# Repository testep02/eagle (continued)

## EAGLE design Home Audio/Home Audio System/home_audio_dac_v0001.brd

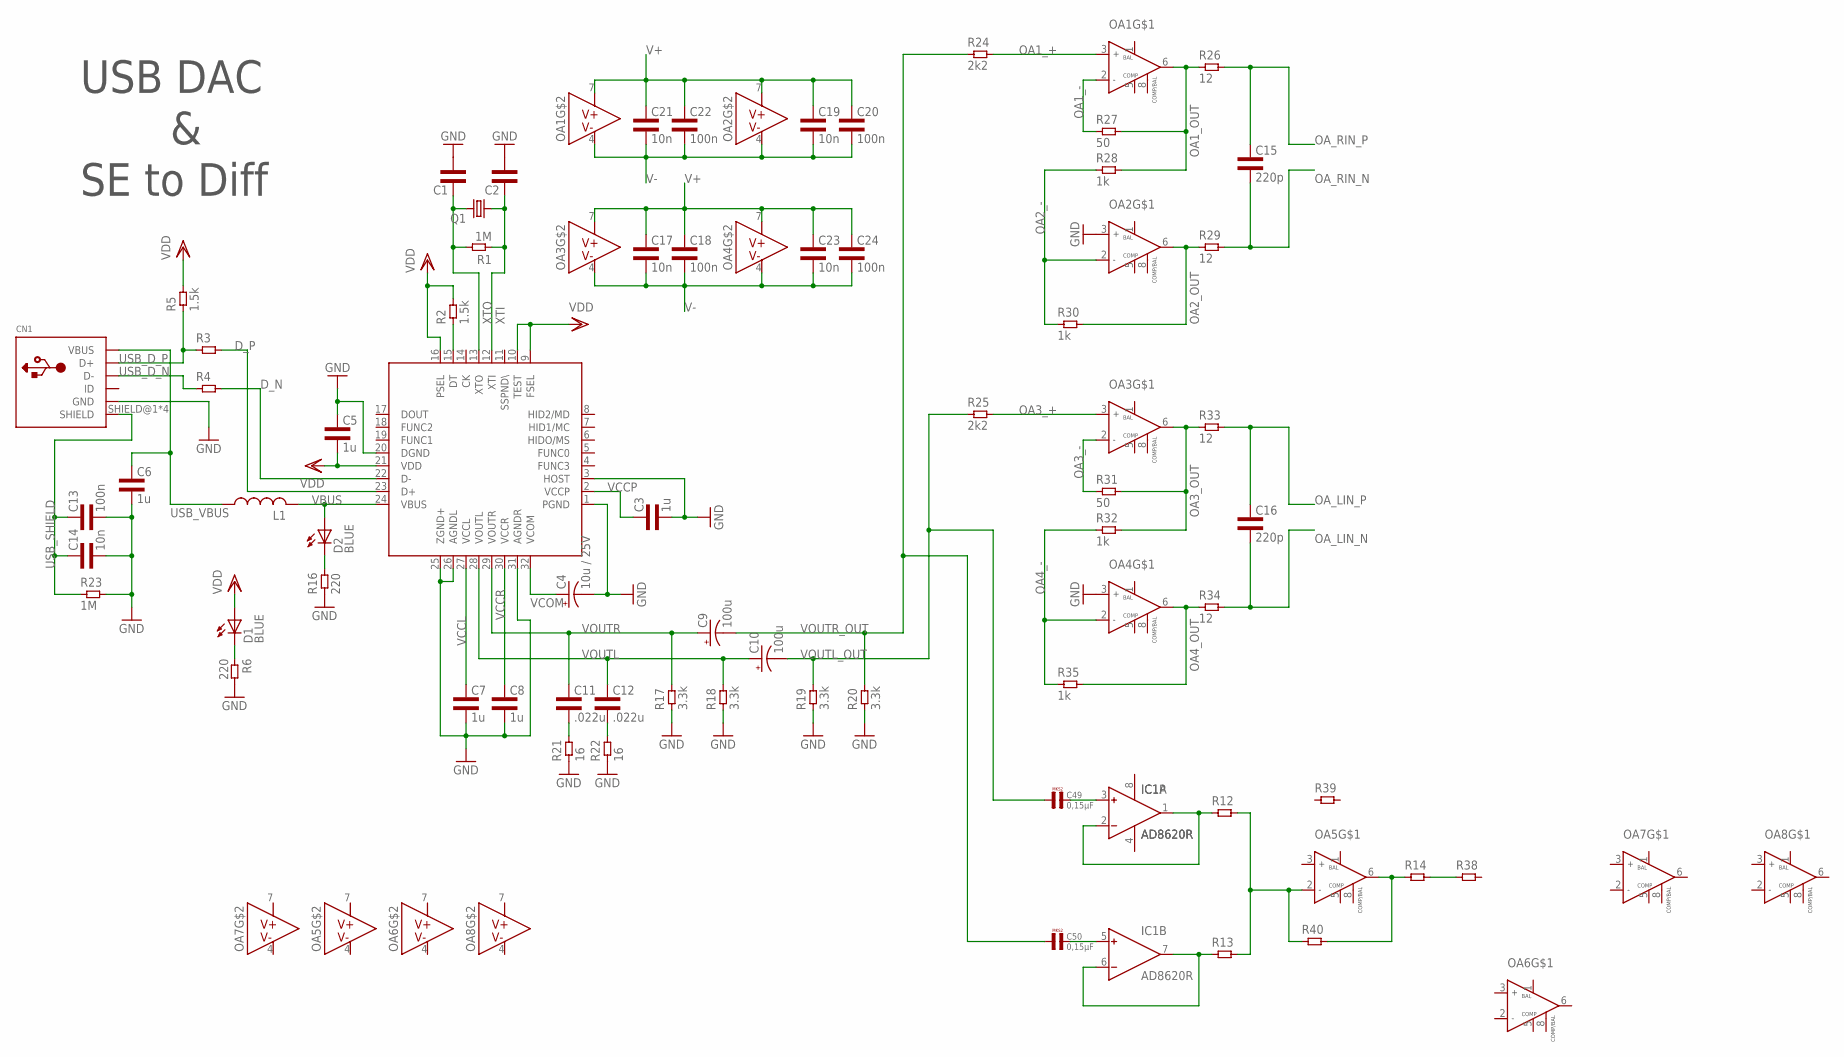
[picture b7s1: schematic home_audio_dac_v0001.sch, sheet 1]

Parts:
C1, C2: CAP0603L3; 0603L3
C3, C5, C6, C7, C8: 1u; 0603L3
C4: 10u / 25V; E1,8-4
C9, C10: 100u; E2-5
C11, C12: .022u; 0603L3
C13, C18, C20, C22, C24: 100n; 0603L3
C14, C17, C19, C21, C23: 10n; 0603L3
C15, C16: 220p; 0603L3
C49, C50: 0,15µF; R5B2K5
CN1: USBMINIB; USB-MINIB
D1, D2: BLUE; LED-0603
IC1: AD8620R; SO8
L1: RCL_L-USL3225M; RCL_L3225M
OA1, OA2, OA3, OA4: NE5534ADSOIC8; SOIC-8
OA5, OA6, OA7, OA8: NE5534SOIC8; SOIC-8
Q1: PCM2707_V1_SPARKFUN_CRYSTALHC49US; PCM2707_V1_SPARKFUN_HC49US
R1, R23: 1M; 0603L3
R2, R5: 1.5k; 0603L3
R3, R4, R12, R13, R14, R38, R39, R40: RES0603L3; 0603L3
R6, R16: 220; 0603L3
R17, R18, R19, R20: 3.3k; 0603L3
R21, R22: 16; 0603L3
R24, R25: 2k2; 0603L3
R26, R29, R33, R34: 12; 0603L3
R27, R31: 50; 0603L3
R28, R30, R32, R35: 1k; 0603L3
U$1: PCM2707_V1_PCM2704C_PCM2707

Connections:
DT: R2.P$1 (1), U$1.15 (DT)
D_N: R4.P$2 (2), U$1.22 (D-)
D_P: R3.P$2 (2), U$1.23 (D+)
GND: C1.P$2 (2), C2.P$2 (2), C3.P$2 (2), C4.-, C5.P$1 (1), C6.P$2 (2), C7.P$2 (2), C8.P$2 (2), C13.P$2 (2), C14.P$2 (2), CN1.GND, OA2.3 (IN+), OA4.3 (IN+), R6.P$2 (2), R16.P$1 (1), R17.P$1 (1), R18.P$1 (1), R19.P$1 (1), R20.P$1 (1), R21.P$1 (1), R22.P$1 (1), R23.P$2 (2), U$1.1 (PGND), U$1.3 (HOST), U$1.20 (DGND), U$1.25 (ZGND+), U$1.26 (AGNDL), U$1.31 (AGNDR); also elsewhere on the board
unnamed: C49.2, IC1.3 (IN+)
unnamed: C50.2, IC1.5 (IN+)
unnamed: IC1.1 (OUT), IC1.2 (IN-), R12.P$1 (1)
unnamed: IC1.6 (IN-), IC1.7 (OUT), R13.P$1 (1)
unnamed: OA5.2 (IN-), R12.P$2 (2), R13.P$2 (2), R40.P$1 (1)
unnamed: OA5.6 (OUT), R14.P$1 (1), R40.P$2 (2)
unnamed: R14.P$2 (2), R38.P$1 (1)
unnamed: D2.C, R16.P$2 (2)
OA1_+: OA1.3 (IN+), R24.P$2 (2)
OA1_-: OA1.2 (IN-), R27.P$1 (1)
OA1_OUT: OA1.6 (OUT), R26.P$1 (1), R27.P$2 (2), R28.P$2 (2)
OA2_-: OA2.2 (IN-), R28.P$1 (1), R30.P$1 (1)
OA2_OUT: OA2.6 (OUT), R29.P$1 (1), R30.P$2 (2)
OA3_+: OA3.3 (IN+), R25.P$2 (2)
OA3_-: OA3.2 (IN-), R31.P$1 (1)
OA3_OUT: OA3.6 (OUT), R31.P$2 (2), R32.P$2 (2), R33.P$1 (1)
OA4_-: OA4.2 (IN-), R32.P$1 (1), R35.P$1 (1)
OA4_OUT: OA4.6 (OUT), R34.P$1 (1), R35.P$2 (2)
OA_LIN_N: C16.P$2 (2), R34.P$2 (2); also elsewhere on the board
OA_LIN_P: C16.P$1 (1), R33.P$2 (2); also elsewhere on the board
OA_RIN_N: C15.P$2 (2), R29.P$2 (2); also elsewhere on the board
OA_RIN_P: C15.P$1 (1), R26.P$2 (2); also elsewhere on the board
USB_D_N: CN1.D-, R4.P$1 (1)
USB_D_P: CN1.D+, R3.P$1 (1), R5.P$1 (1)
USB_SHIELD: C13.P$1 (1), C14.P$1 (1), CN1.SHIELD@1 (SHIELD), CN1.SHIELD@2 (SHIELD), CN1.SHIELD@3 (SHIELD), CN1.SHIELD@4 (SHIELD), R23.P$1 (1)
USB_VBUS: C6.P$1 (1), CN1.VBUS, L1.1
V+: C17.P$1 (1), C18.P$1 (1), C19.P$1 (1), C20.P$1 (1), C21.P$1 (1), C22.P$1 (1), C23.P$1 (1), C24.P$1 (1), IC1.8 (V+), OA1.7 (V+), OA2.7 (V+), OA3.7 (V+), OA4.7 (V+), OA5.7 (V+), OA6.7 (V+), OA7.7 (V+), OA8.7 (V+)
V-: C17.P$2 (2), C18.P$2 (2), C19.P$2 (2), C20.P$2 (2), C21.P$2 (2), C22.P$2 (2), C23.P$2 (2), C24.P$2 (2), IC1.4 (V-), OA1.4 (V-), OA2.4 (V-), OA3.4 (V-), OA4.4 (V-), OA5.4 (V-), OA6.4 (V-), OA7.4 (V-), OA8.4 (V-)
VBUS: D2.A, L1.2, U$1.24 (VBUS)
VCCL: C7.P$1 (1), U$1.27 (VCCL)
VCCP: C3.P$1 (1), U$1.2 (VCCP)
VCCR: C8.P$1 (1), U$1.30 (VCCR)
VCOM: C4.+, U$1.32 (VCOM)
VDD: C5.P$2 (2), D1.A, R2.P$2 (2), R5.P$2 (2), U$1.9 (FSEL), U$1.10 (TEST), U$1.16 (PSEL), U$1.21 (VDD)
VDD_LED: D1.C, R6.P$1 (1)
VOUTL: C10.+, C12.P$1 (1), R18.P$2 (2), U$1.28 (VOUTL)
VOUTL_CAP: C12.P$2 (2), R22.P$2 (2)
VOUTL_OUT: C10.-, C49.1, R19.P$2 (2), R25.P$1 (1)
VOUTR: C9.+, C11.P$1 (1), R17.P$2 (2), U$1.29 (VOUTR)
VOUTR_CAP: C11.P$2 (2), R21.P$2 (2)
VOUTR_OUT: C9.-, C50.1, R20.P$2 (2), R24.P$1 (1)
XTI: C2.P$1 (1), Q1.1, R1.P$1 (1), U$1.12 (XTI)
XTO: C1.P$1 (1), Q1.2, R1.P$2 (2), U$1.13 (XTO)

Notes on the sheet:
USB DAC
SE to Diff

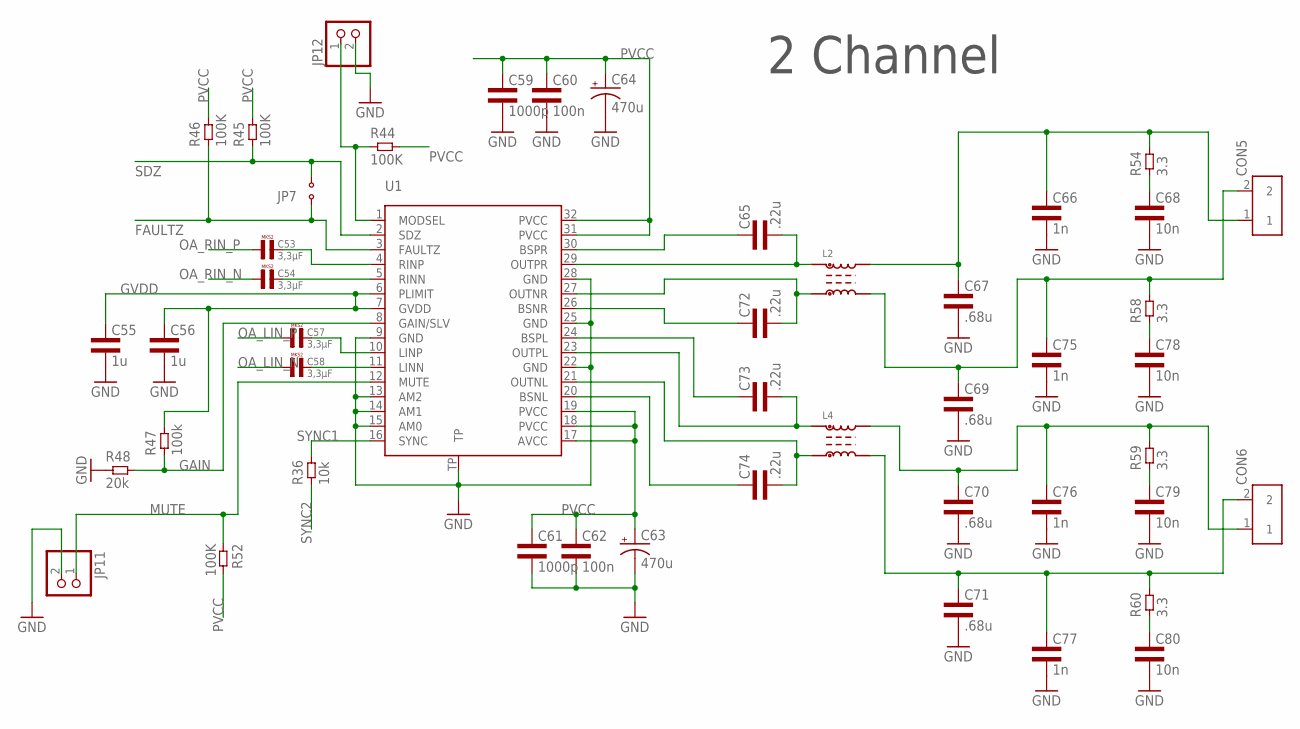
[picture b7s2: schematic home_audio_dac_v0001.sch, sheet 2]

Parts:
C53, C54, C57, C58: 3,3µF; R5B5K5
C55, C56: 1u; 0603L3
C59, C61: 1000p; 0805L3
C60, C62: 100n; 0805L3
C63, C64: 470u; PANASONIC_F
C65, C72, C73, C74: .22u; 0805L3
C66, C75, C76, C77: 1n; 0603L3
C67, C69, C70, C71: .68u; 1206L3
C68, C78, C79, C80: 10n; 0805L3
CON5, CON6: TERM_BLOCK_2
JP7: JUMPER2
JP11, JP12: PINHD-1X2; 1X02
L2, L4: 1155EA
R36: 10k; 0603L3
R44, R45, R46, R52: 100K; 0603L3
R47: 100k; 0603L3
R48: 20k; 0603L3
R54, R58, R59, R60: 3.3; 0805L3
U1: TPA3116; R-PDSO-32

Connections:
FAULTZ: JP7.1, R46.P$1 (1), U1.3 (FAULTZ); also elsewhere on the board
GAIN: R47.P$1 (1), R48.P$2 (2), U1.8 (GAIN/SLV); also elsewhere on the board
GND: C55.P$2 (2), C56.P$2 (2), C59.2, C60.2, C61.2, C62.2, C63.-, C64.-, C66.P$2 (2), C67.2, C68.2, C69.2, C70.2, C71.2, C75.P$2 (2), C76.P$2 (2), C77.P$2 (2), C78.2, C79.2, C80.2, JP11.2, JP12.2, R48.P$1 (1), U1.9 (GND), U1.13 (AM2), U1.14 (AM1), U1.15 (AM0), U1.22 (GND), U1.25 (GND), U1.28 (GND), U1.TP; also elsewhere on the board
GVDD: C55.P$1 (1), C56.P$1 (1), R47.P$2 (2), U1.6 (PLIMIT), U1.7 (GVDD); also elsewhere on the board
LIN_CAP1_N: C58.2, U1.11 (LINN)
LIN_CAP1_P: C57.2, U1.10 (LINP)
MODSEL1: JP12.1, R44.P$1 (1), U1.1 (MODSEL)
MUTE: JP11.1, R52.P$1 (1), U1.12 (MUTE); also elsewhere on the board
unnamed: C65.1, U1.30 (BSPR)
unnamed: C65.2, L2.4, U1.29 (OUTPR)
unnamed: C66.P$1 (1), C67.1, CON5.1, L2.3, R54.2
unnamed: C68.1, R54.1
unnamed: C72.1, U1.26 (BSNR)
unnamed: C73.1, U1.24 (BSPL)
unnamed: C74.1, U1.20 (BSNL)
unnamed: C72.2, L2.1, U1.27 (OUTNR)
unnamed: C73.2, L4.4, U1.23 (OUTPL)
unnamed: C74.2, L4.1, U1.21 (OUTNL)
unnamed: C69.1, C75.P$1 (1), CON5.2, L2.2, R58.2
unnamed: C70.1, C76.P$1 (1), CON6.1, L4.3, R59.2
unnamed: C71.1, C77.P$1 (1), CON6.2, L4.2, R60.2
unnamed: C78.1, R58.1
unnamed: C79.1, R59.1
unnamed: C80.1, R60.1
OA_LIN_N: C58.1; also elsewhere on the board
OA_LIN_P: C57.1; also elsewhere on the board
OA_RIN_N: C54.1; also elsewhere on the board
OA_RIN_P: C53.1; also elsewhere on the board
PVCC: C59.1, C60.1, C61.1, C62.1, C63.+, C64.+, R44.P$2 (2), R45.P$2 (2), R46.P$2 (2), R52.P$2 (2), U1.17 (AVCC), U1.18 (PVCC), U1.19 (PVCC), U1.31 (PVCC), U1.32 (PVCC); also elsewhere on the board
RIN_CAP1_N: C54.2, U1.5 (RINN)
RIN_CAP1_P: C53.2, U1.4 (RINP)
SDZ: JP7.2, R45.P$1 (1), U1.2 (SDZ); also elsewhere on the board
SYNC1: R36.P$2 (2), U1.16 (SYNC)
SYNC2: R36.P$1 (1); also elsewhere on the board

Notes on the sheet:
2 Channel

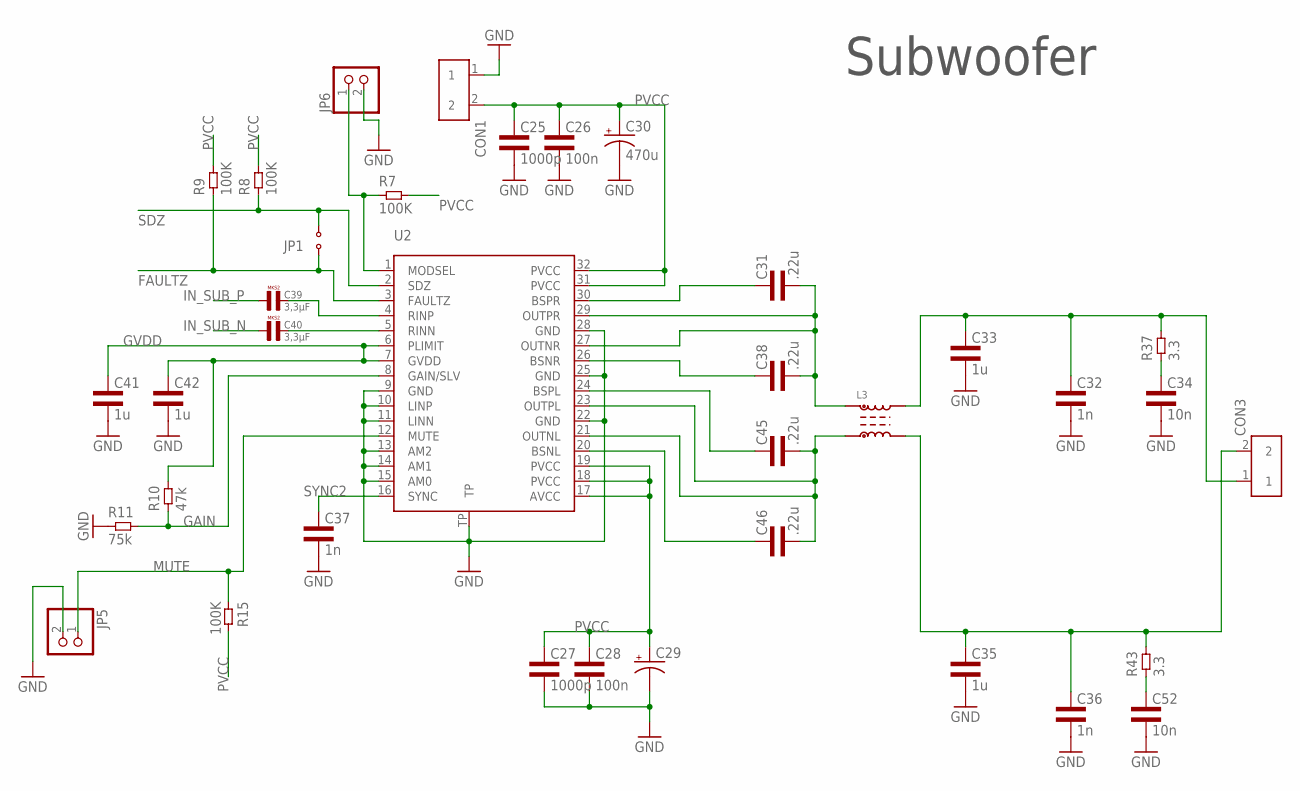
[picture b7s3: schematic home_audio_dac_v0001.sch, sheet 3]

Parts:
C25, C27: 1000p; 0805L3
C26, C28: 100n; 0805L3
C29: CPOL-USF; PANASONIC_F
C30: 470u; PANASONIC_F
C31, C38, C45, C46: .22u; 0805L3
C32, C36, C37: 1n; 0603L3
C33, C35: 1u; 1206L3
C34, C52: 10n; 0805L3
C39, C40: 3,3µF; R5B5K5
C41, C42: 1u; 0603L3
CON1, CON3: TERM_BLOCK_2
JP1: JUMPER2
JP5, JP6: PINHD-1X2; 1X02
L3: 1155EA
R7, R8, R9, R15: 100K; 0603L3
R10: 47k; 0603L3
R11: 75k; 0603L3
R37, R43: 3.3; 0805L3
U2: TPA3116; R-PDSO-32

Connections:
FAULTZ: JP1.1, R9.P$1 (1), U2.3 (FAULTZ); also elsewhere on the board
GAIN: R10.P$1 (1), R11.P$2 (2), U2.8 (GAIN/SLV); also elsewhere on the board
GND: C25.2, C26.2, C27.2, C28.2, C29.-, C30.-, C32.P$2 (2), C33.2, C34.2, C35.2, C36.P$2 (2), C37.P$2 (2), C41.P$2 (2), C42.P$2 (2), C52.2, CON1.1, JP5.2, JP6.2, R11.P$1 (1), U2.9 (GND), U2.10 (LINP), U2.11 (LINN), U2.13 (AM2), U2.14 (AM1), U2.15 (AM0), U2.22 (GND), U2.25 (GND), U2.28 (GND), U2.TP; also elsewhere on the board
GVDD: C41.P$1 (1), C42.P$1 (1), R10.P$2 (2), U2.6 (PLIMIT), U2.7 (GVDD); also elsewhere on the board
IN_SUB_CAP_N: C40.2, U2.5 (RINN)
IN_SUB_CAP_P: C39.2, U2.4 (RINP)
IN_SUB_N: C40.1
IN_SUB_P: C39.1
MODSEL: JP6.1, R7.P$1 (1), U2.1 (MODSEL)
MUTE: JP5.1, R15.P$1 (1), U2.12 (MUTE); also elsewhere on the board
unnamed: C31.1, U2.30 (BSPR)
unnamed: C31.2, C38.2, L3.4, U2.27 (OUTNR), U2.29 (OUTPR)
unnamed: C32.P$1 (1), C33.1, CON3.1, L3.3, R37.2
unnamed: C34.1, R37.1
unnamed: C38.1, U2.26 (BSNR)
unnamed: C45.1, U2.24 (BSPL)
unnamed: C46.1, U2.20 (BSNL)
unnamed: C45.2, C46.2, L3.1, U2.21 (OUTNL), U2.23 (OUTPL)
unnamed: C35.1, C36.P$1 (1), CON3.2, L3.2, R43.2
unnamed: C52.1, R43.1
PVCC: C25.1, C26.1, C27.1, C28.1, C29.+, C30.+, CON1.2, R7.P$2 (2), R8.P$2 (2), R9.P$2 (2), R15.P$2 (2), U2.17 (AVCC), U2.18 (PVCC), U2.19 (PVCC), U2.31 (PVCC), U2.32 (PVCC); also elsewhere on the board
SDZ: JP1.2, R8.P$1 (1), U2.2 (SDZ); also elsewhere on the board
SYNC2: C37.P$1 (1), U2.16 (SYNC); also elsewhere on the board

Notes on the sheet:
Subwoofer

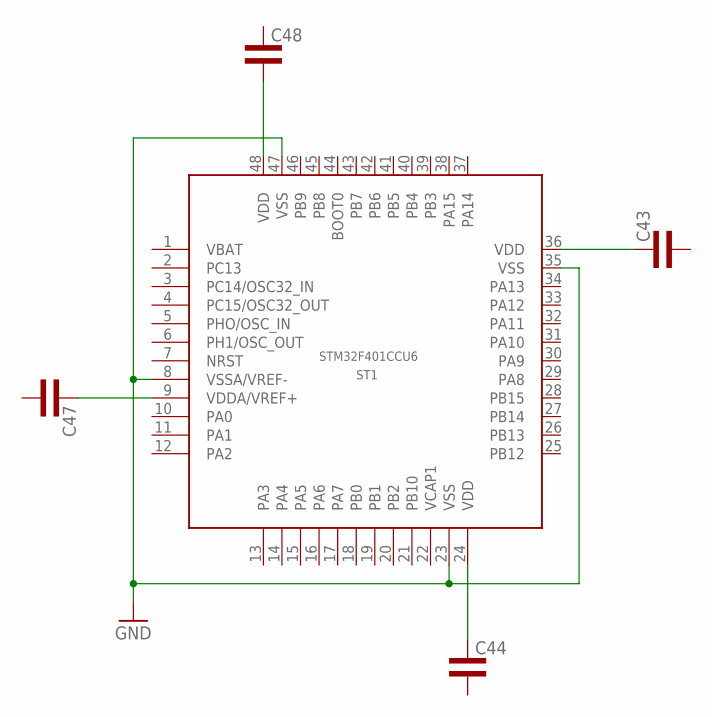
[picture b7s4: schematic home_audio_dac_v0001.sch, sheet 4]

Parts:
C43, C44, C47, C48: CAP0603L3; 0603L3
ST1: STM32F401CCU6; UFQFPN48

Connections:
GND: ST1.8 (VSSA/VREF-), ST1.23 (VSS), ST1.35 (VSS), ST1.47 (VSS); also elsewhere on the board
unnamed: C48.P$2 (2), ST1.48 (VDD)
unnamed: C47.P$1 (1), ST1.9 (VDDA/VREF+)
unnamed: C44.P$1 (1), ST1.24 (VDD)
unnamed: C43.P$1 (1), ST1.36 (VDD)

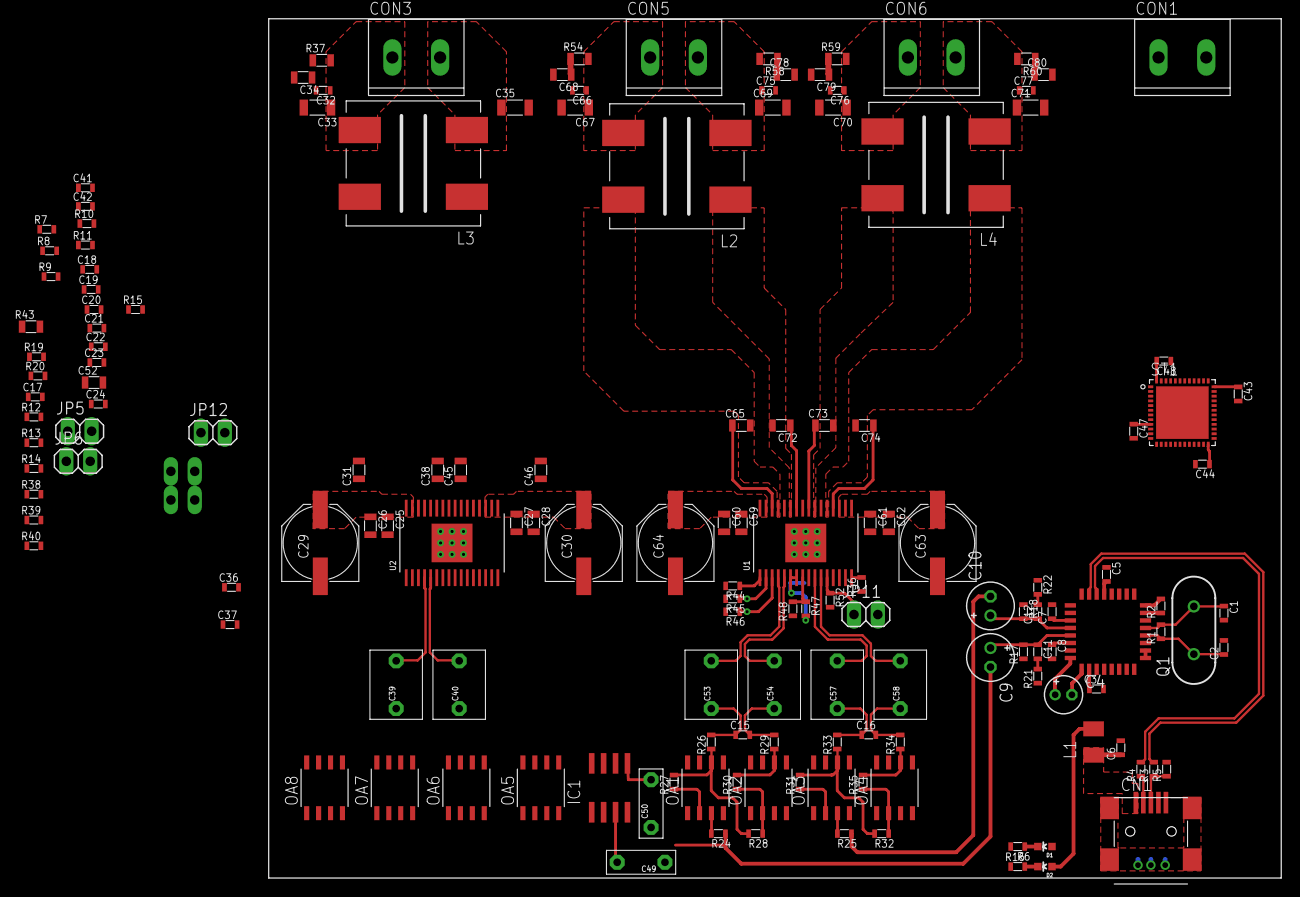
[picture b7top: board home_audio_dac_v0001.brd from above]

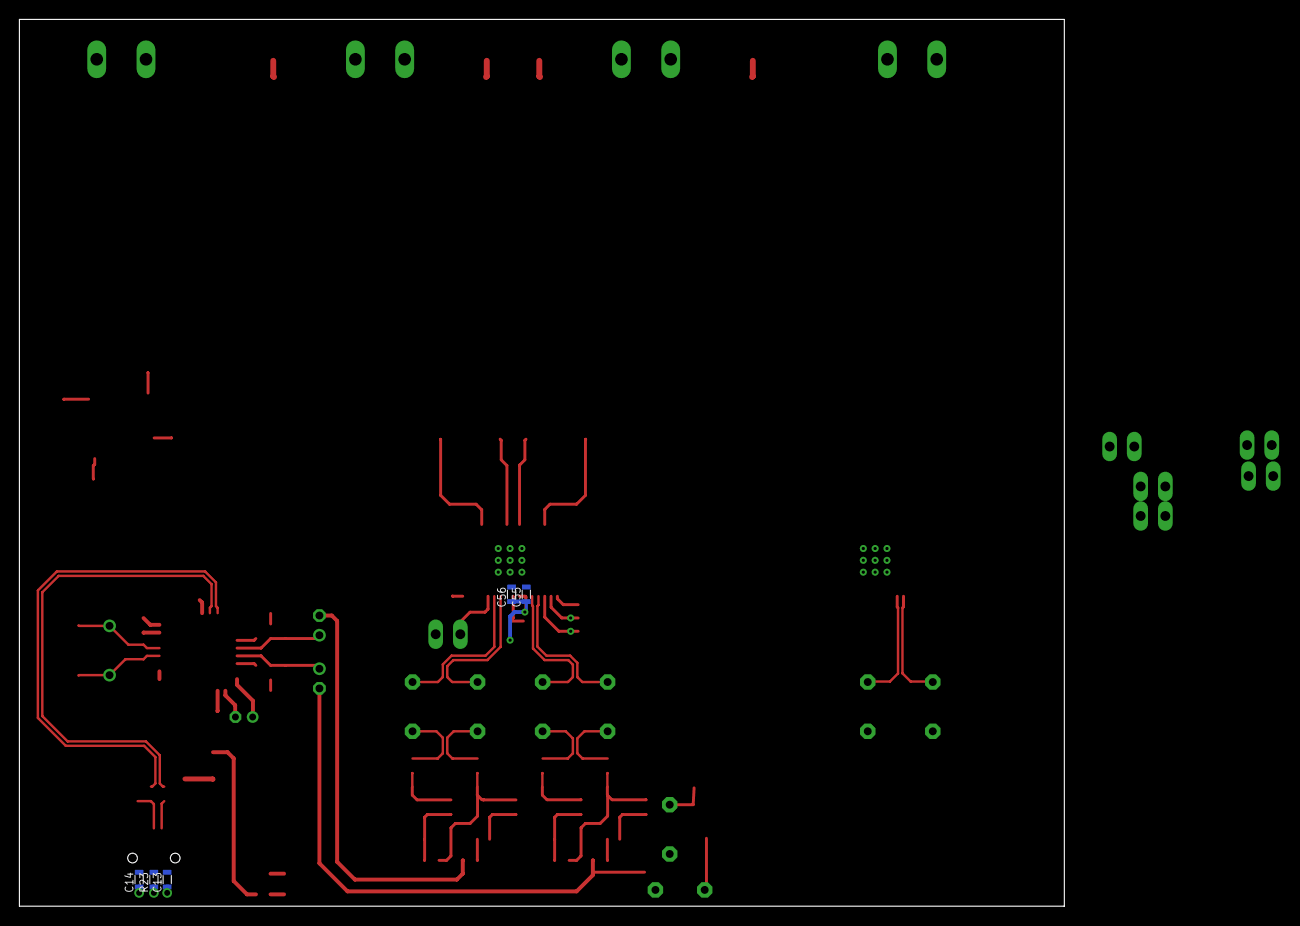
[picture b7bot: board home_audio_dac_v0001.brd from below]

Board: 2 copper layers, 107.7 x 91.4 mm, 161 parts (5 on the bottom side), 93 nets.

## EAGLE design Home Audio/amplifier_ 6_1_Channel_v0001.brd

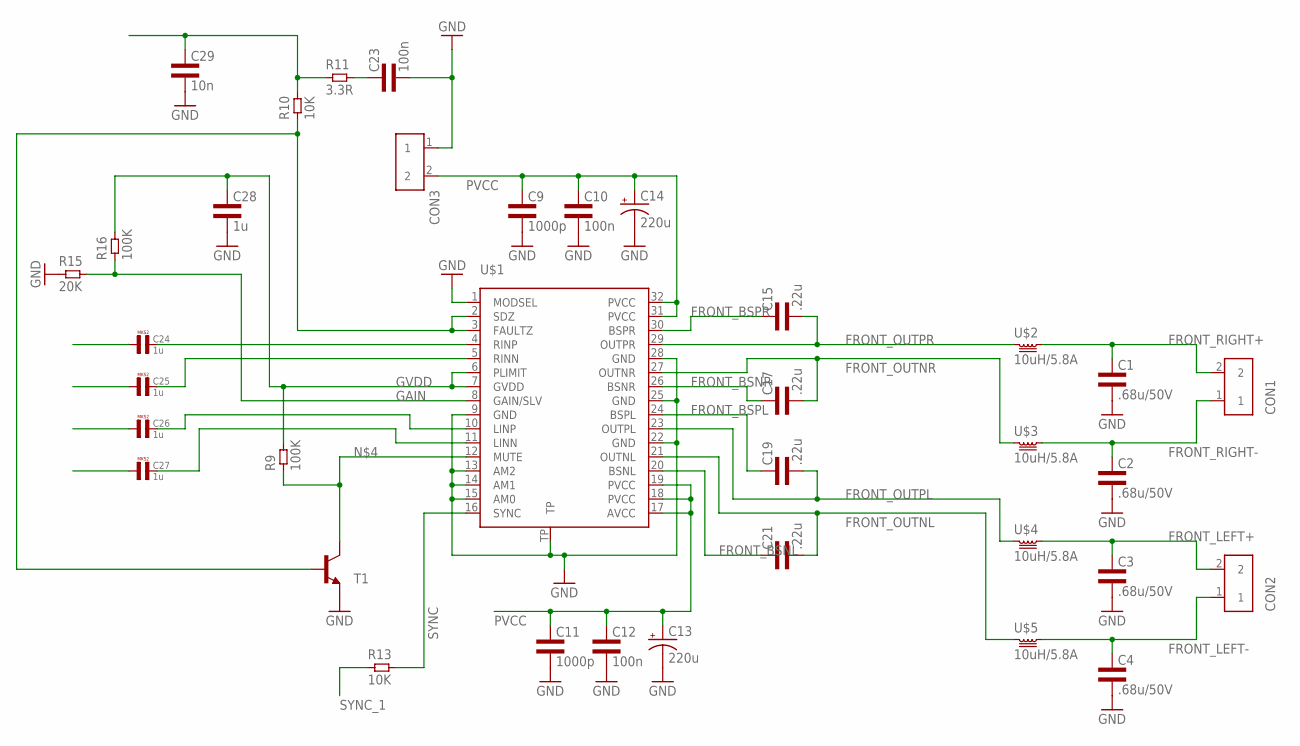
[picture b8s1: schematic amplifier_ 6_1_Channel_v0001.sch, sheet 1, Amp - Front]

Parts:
C1, C2, C3, C4: .68u/50V; 1206L3
C9, C11: 1000p; 0603L3
C10, C12, C23: 100n; 0603L3
C13, C14: 220u; PANASONIC_G
C15, C17, C19, C21: .22u; 0603L3
C24, C25, C26, C27: 1u; R5B8K5
C28: 1u; 0603L3
C29: 10n; 0603L3
CON1, CON2, CON3: TERM_BLOCK_2
R9, R16: 100K; 0603L3
R10, R13: 10K; 0603L3
R11: 3.3R; 0603L3
R15: 20K; 0603L3
T1: TRANSISTOR_MMBT2222ALT1-NPN-SOT23-BEC; TRANSISTOR_SOT23-BEC
U$1: TPA3116; R-PDSO-32
U$2, U$3, U$4, U$5: 10uH/5.8A; DR127

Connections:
FRONT_BSNL: C21.P$1 (1), U$1.20 (BSNL)
FRONT_BSNR: C17.P$1 (1), U$1.26 (BSNR)
FRONT_BSPL: C19.P$1 (1), U$1.24 (BSPL)
FRONT_BSPR: C15.P$1 (1), U$1.30 (BSPR)
FRONT_LEFT+: C3.1, CON2.2, U$4.2
FRONT_LEFT-: C4.1, CON2.1, U$5.2
FRONT_OUTNL: C21.P$2 (2), U$1.21 (OUTNL), U$5.1
FRONT_OUTNR: C17.P$2 (2), U$1.27 (OUTNR), U$3.1
FRONT_OUTPL: C19.P$2 (2), U$1.23 (OUTPL), U$4.1
FRONT_OUTPR: C15.P$2 (2), U$1.29 (OUTPR), U$2.1
FRONT_RIGHT+: C1.1, CON1.2, U$2.2
FRONT_RIGHT-: C2.1, CON1.1, U$3.2
GAIN: R15.P$2 (2), R16.P$1 (1), U$1.8 (GAIN/SLV); also elsewhere on the board
GND: C1.2, C2.2, C3.2, C4.2, C9.P$2 (2), C10.P$2 (2), C11.P$2 (2), C12.P$2 (2), C13.-, C14.-, C23.P$2 (2), C28.P$2 (2), C29.P$2 (2), CON3.1, R15.P$1 (1), T1.E, U$1.1 (MODSEL), U$1.9 (GND), U$1.13 (AM2), U$1.14 (AM1), U$1.15 (AM0), U$1.22 (GND), U$1.25 (GND), U$1.28 (GND), U$1.TP; also elsewhere on the board
GVDD: C28.P$1 (1), R9.P$2 (2), R16.P$2 (2), U$1.6 (PLIMIT), U$1.7 (GVDD); also elsewhere on the board
MUTE: R10.P$1 (1), T1.B, U$1.2 (SDZ), U$1.3 (FAULTZ); also elsewhere on the board
unnamed: C27.2, U$1.11 (LINN)
unnamed: C26.2, U$1.10 (LINP)
unnamed: C24.2, U$1.4 (RINP)
unnamed: R9.P$1 (1), T1.C, U$1.12 (MUTE)
unnamed: C25.2, U$1.5 (RINN)
unnamed: C29.P$1 (1), R10.P$2 (2), R11.P$1 (1)
unnamed: C23.P$1 (1), R11.P$2 (2)
PVCC: C9.P$1 (1), C10.P$1 (1), C11.P$1 (1), C12.P$1 (1), C13.+, C14.+, CON3.2, U$1.17 (AVCC), U$1.18 (PVCC), U$1.19 (PVCC), U$1.31 (PVCC), U$1.32 (PVCC); also elsewhere on the board
SYNC: R13.P$2 (2), U$1.16 (SYNC)
SYNC_1: R13.P$1 (1); also elsewhere on the board

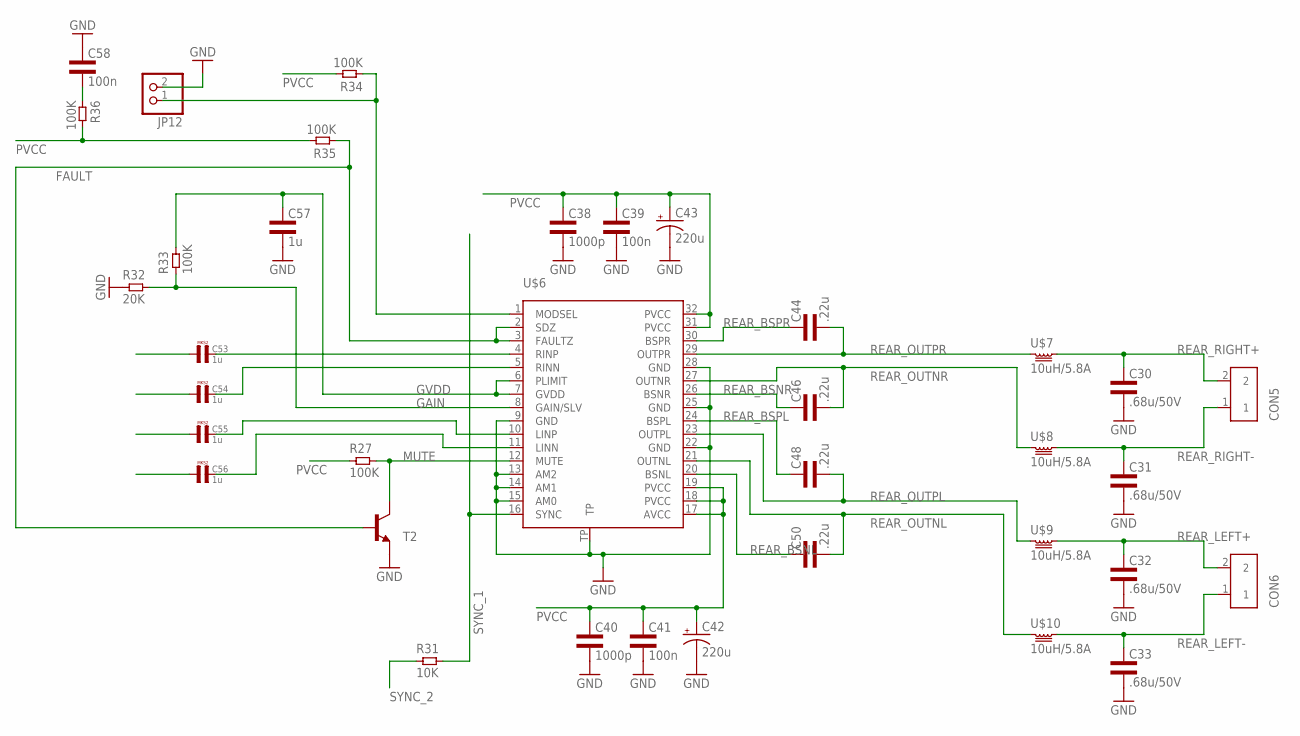
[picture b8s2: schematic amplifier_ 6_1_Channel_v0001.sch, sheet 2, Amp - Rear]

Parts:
C30, C31, C32, C33: .68u/50V; 1206L3
C38, C40: 1000p; 0603L3
C39, C41, C58: 100n; 0603L3
C42, C43: 220u; PANASONIC_G
C44, C46, C48, C50: .22u; 0603L3
C53, C54, C55, C56: 1u; R5B8K5
C57: 1u; 0603L3
CON5, CON6: TERM_BLOCK_2
JP12: PINHD-1X2; 1X02
R27, R33, R34, R35, R36: 100K; 0603L3
R31: 10K; 0603L3
R32: 20K; 0603L3
T2: TRANSISTOR_MMBT2222ALT1-NPN-SOT23-BEC; TRANSISTOR_SOT23-BEC
U$6: TPA3116; R-PDSO-32
U$7, U$8, U$9, U$10: 10uH/5.8A; DR127

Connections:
FAULT: R35.P$1 (1), T2.B, U$6.2 (SDZ), U$6.3 (FAULTZ); also elsewhere on the board
GAIN: R32.P$2 (2), R33.P$1 (1), U$6.8 (GAIN/SLV); also elsewhere on the board
GND: C30.2, C31.2, C32.2, C33.2, C38.P$2 (2), C39.P$2 (2), C40.P$2 (2), C41.P$2 (2), C42.-, C43.-, C57.P$2 (2), C58.P$1 (1), JP12.2, R32.P$1 (1), T2.E, U$6.9 (GND), U$6.13 (AM2), U$6.14 (AM1), U$6.15 (AM0), U$6.22 (GND), U$6.25 (GND), U$6.28 (GND), U$6.TP; also elsewhere on the board
GVDD: C57.P$1 (1), R33.P$2 (2), U$6.6 (PLIMIT), U$6.7 (GVDD); also elsewhere on the board
MUTE: R27.P$2 (2), T2.C, U$6.12 (MUTE); also elsewhere on the board
unnamed: C56.2, U$6.11 (LINN)
unnamed: C55.2, U$6.10 (LINP)
unnamed: C53.2, U$6.4 (RINP)
unnamed: C54.2, U$6.5 (RINN)
unnamed: JP12.1, R34.P$1 (1), U$6.1 (MODSEL)
unnamed: C58.P$2 (2), R36.P$1 (1)
PVCC: C38.P$1 (1), C39.P$1 (1), C40.P$1 (1), C41.P$1 (1), C42.+, C43.+, R27.P$1 (1), R34.P$2 (2), R35.P$2 (2), R36.P$2 (2), U$6.17 (AVCC), U$6.18 (PVCC), U$6.19 (PVCC), U$6.31 (PVCC), U$6.32 (PVCC); also elsewhere on the board
REAR_BSNL: C50.P$1 (1), U$6.20 (BSNL)
REAR_BSNR: C46.P$1 (1), U$6.26 (BSNR)
REAR_BSPL: C48.P$1 (1), U$6.24 (BSPL)
REAR_BSPR: C44.P$1 (1), U$6.30 (BSPR)
REAR_LEFT+: C32.1, CON6.2, U$9.2
REAR_LEFT-: C33.1, CON6.1, U$10.2
REAR_OUTNL: C50.P$2 (2), U$6.21 (OUTNL), U$10.1
REAR_OUTNR: C46.P$2 (2), U$6.27 (OUTNR), U$8.1
REAR_OUTPL: C48.P$2 (2), U$6.23 (OUTPL), U$9.1
REAR_OUTPR: C44.P$2 (2), U$6.29 (OUTPR), U$7.1
REAR_RIGHT+: C30.1, CON5.2, U$7.2
REAR_RIGHT-: C31.1, CON5.1, U$8.2
SYNC_1: R31.P$2 (2), U$6.16 (SYNC); also elsewhere on the board
SYNC_2: R31.P$1 (1); also elsewhere on the board

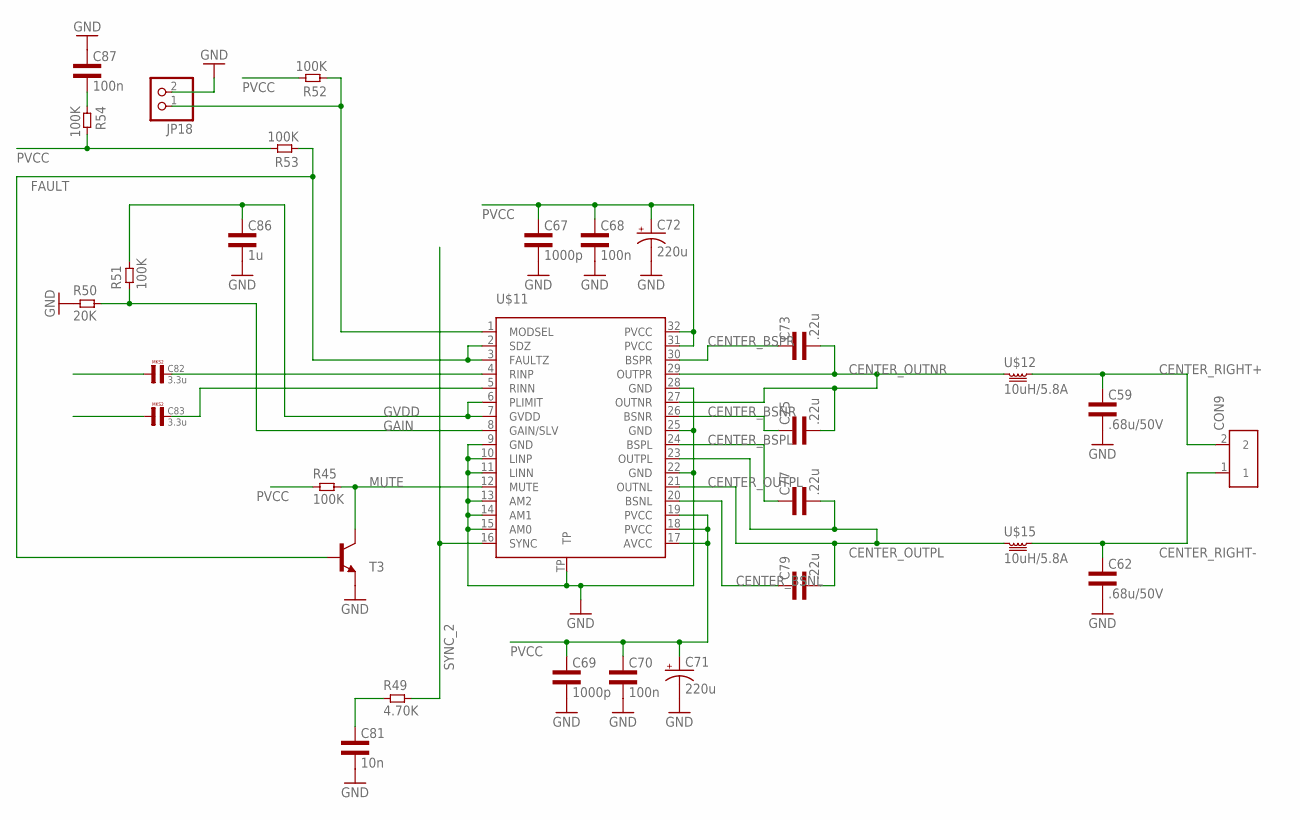
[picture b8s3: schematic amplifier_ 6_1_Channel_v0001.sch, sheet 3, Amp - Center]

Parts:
C59, C62: .68u/50V; 1206L3
C67, C69: 1000p; 0603L3
C68, C70, C87: 100n; 0603L3
C71, C72: 220u; PANASONIC_G
C73, C75, C77, C79: .22u; 0603L3
C81: 10n; 0603L3
C82, C83: 3.3u; R5B8K5
C86: 1u; 0603L3
CON9: TERM_BLOCK_2
JP18: PINHD-1X2; 1X02
R45, R51, R52, R53, R54: 100K; 0603L3
R49: 4.70K; 0603L3
R50: 20K; 0603L3
T3: TRANSISTOR_MMBT2222ALT1-NPN-SOT23-BEC; TRANSISTOR_SOT23-BEC
U$11: TPA3116; R-PDSO-32
U$12, U$15: 10uH/5.8A; DR127

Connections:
CENTER_BSNL: C79.P$1 (1), U$11.20 (BSNL)
CENTER_BSNR: C75.P$1 (1), U$11.26 (BSNR)
CENTER_BSPL: C77.P$1 (1), U$11.24 (BSPL)
CENTER_BSPR: C73.P$1 (1), U$11.30 (BSPR)
CENTER_OUTNR: C73.P$2 (2), C75.P$2 (2), U$11.27 (OUTNR), U$11.29 (OUTPR), U$12.1
CENTER_OUTPL: C77.P$2 (2), C79.P$2 (2), U$11.21 (OUTNL), U$11.23 (OUTPL), U$15.1
CENTER_RIGHT+: C59.1, CON9.2, U$12.2
CENTER_RIGHT-: C62.1, CON9.1, U$15.2
FAULT: R53.P$1 (1), T3.B, U$11.2 (SDZ), U$11.3 (FAULTZ); also elsewhere on the board
GAIN: R50.P$2 (2), R51.P$1 (1), U$11.8 (GAIN/SLV); also elsewhere on the board
GND: C59.2, C62.2, C67.P$2 (2), C68.P$2 (2), C69.P$2 (2), C70.P$2 (2), C71.-, C72.-, C81.P$2 (2), C86.P$2 (2), C87.P$1 (1), JP18.2, R50.P$1 (1), T3.E, U$11.9 (GND), U$11.10 (LINP), U$11.11 (LINN), U$11.13 (AM2), U$11.14 (AM1), U$11.15 (AM0), U$11.22 (GND), U$11.25 (GND), U$11.28 (GND), U$11.TP; also elsewhere on the board
GVDD: C86.P$1 (1), R51.P$2 (2), U$11.6 (PLIMIT), U$11.7 (GVDD); also elsewhere on the board
MUTE: R45.P$2 (2), T3.C, U$11.12 (MUTE); also elsewhere on the board
unnamed: C82.2, U$11.4 (RINP)
unnamed: C83.2, U$11.5 (RINN)
unnamed: JP18.1, R52.P$1 (1), U$11.1 (MODSEL)
unnamed: C87.P$2 (2), R54.P$1 (1)
PVCC: C67.P$1 (1), C68.P$1 (1), C69.P$1 (1), C70.P$1 (1), C71.+, C72.+, R45.P$1 (1), R52.P$2 (2), R53.P$2 (2), R54.P$2 (2), U$11.17 (AVCC), U$11.18 (PVCC), U$11.19 (PVCC), U$11.31 (PVCC), U$11.32 (PVCC); also elsewhere on the board
SYNC_2: R49.P$2 (2), U$11.16 (SYNC); also elsewhere on the board
SYNC_3: C81.P$1 (1), R49.P$1 (1)

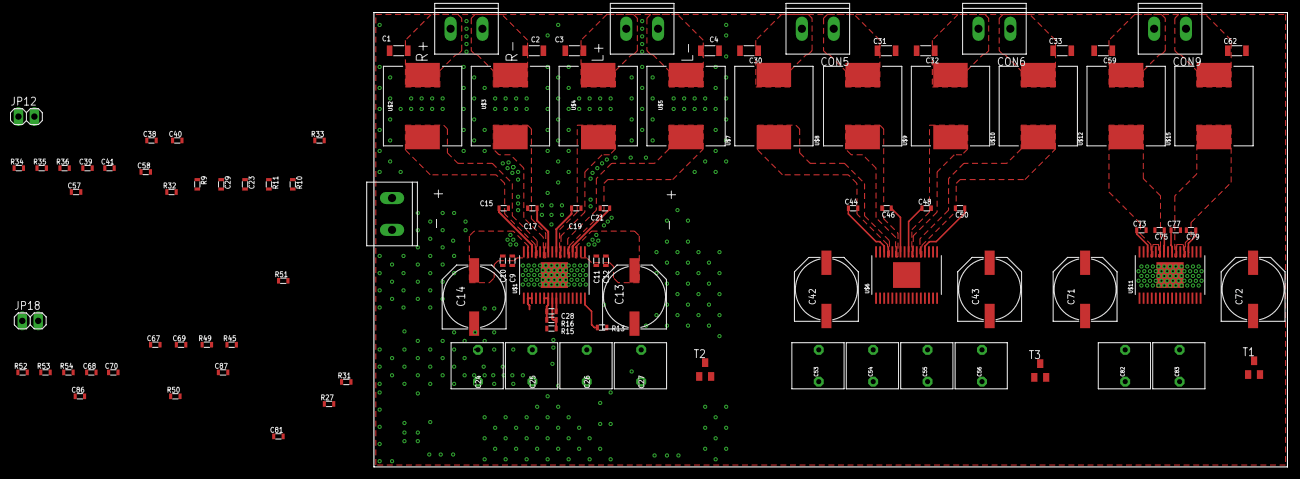
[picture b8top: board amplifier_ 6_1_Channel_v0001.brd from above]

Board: 2 copper layers, 145.8 x 72.5 mm, 102 parts (0 on the bottom side), 59 nets.
